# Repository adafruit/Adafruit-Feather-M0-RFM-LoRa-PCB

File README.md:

## Adafruit Feather M0 RFM LoRa PCB
&nbsp; <br />
Click to purchase from the Adafruit Shop:
- [Adafruit Feather M0 with RFM95 LoRa Radio - 900MHz - RadioFruit](https://www.adafruit.com/product/3178)
- [Adafruit Feather M0 RFM96 LoRa Radio - 433MHz - RadioFruit](https://www.adafruit.com/product/3179)

This is the Adafruit Feather M0 RFM95 LoRa Radio (900MHz). We call these RadioFruits, our take on an microcontroller with a "Long Range (LoRa)" packet radio transceiver with built in USB and battery charging. Its an Adafruit Feather M0 with a 900MHz radio module cooked in! Great for making wireless networks that are more flexible than Bluetooth LE and without the high power requirements of WiFi.

Feather is the new development board from Adafruit, and like its namesake it is thin, light, and lets you fly! We designed Feather to be a new standard for portable microcontroller cores.We have other boards in the Feather family, check'em out here.

This is the 900 MHz radio version, which can be used for either 868MHz or 915MHz transmission/reception - the exact radio frequency is determined when you load the software since it can be tuned around dynamically. We also sell a 433MHz version of the same radio chipset!

At the Feather M0's heart is an ATSAMD21G18 ARM Cortex M0 processor, clocked at 48 MHz and at 3.3V logic, the same one used in the new Arduino Zero. This chip has a whopping 256K of FLASH (8x more than the Atmega328 or 32u4) and 32K of RAM (16x as much)! This chip comes with built in USB so it has USB-to-Serial program & debug capability built in with no need for an FTDI-like chip.

For more details, check out the product pages at

  * https://www.adafruit.com/product/3178
  * https://www.adafruit.com/product/3179
  
PCB files for the Adafruit Feather M0 RFM69 / RFM9X LoRa Radios. The format is EagleCAD schematic and board layout

### License

Adafruit invests time and resources providing this open source design, please support Adafruit and open-source hardware by purchasing products from [Adafruit](https://www.adafruit.com)!

All text above must be included in any redistribution

Designed by Limor Fried/Ladyada for Adafruit Industries.
Creative Commons Attribution/Share-Alike, all text above must be included in any redistribution. 
See license.txt for additional information.

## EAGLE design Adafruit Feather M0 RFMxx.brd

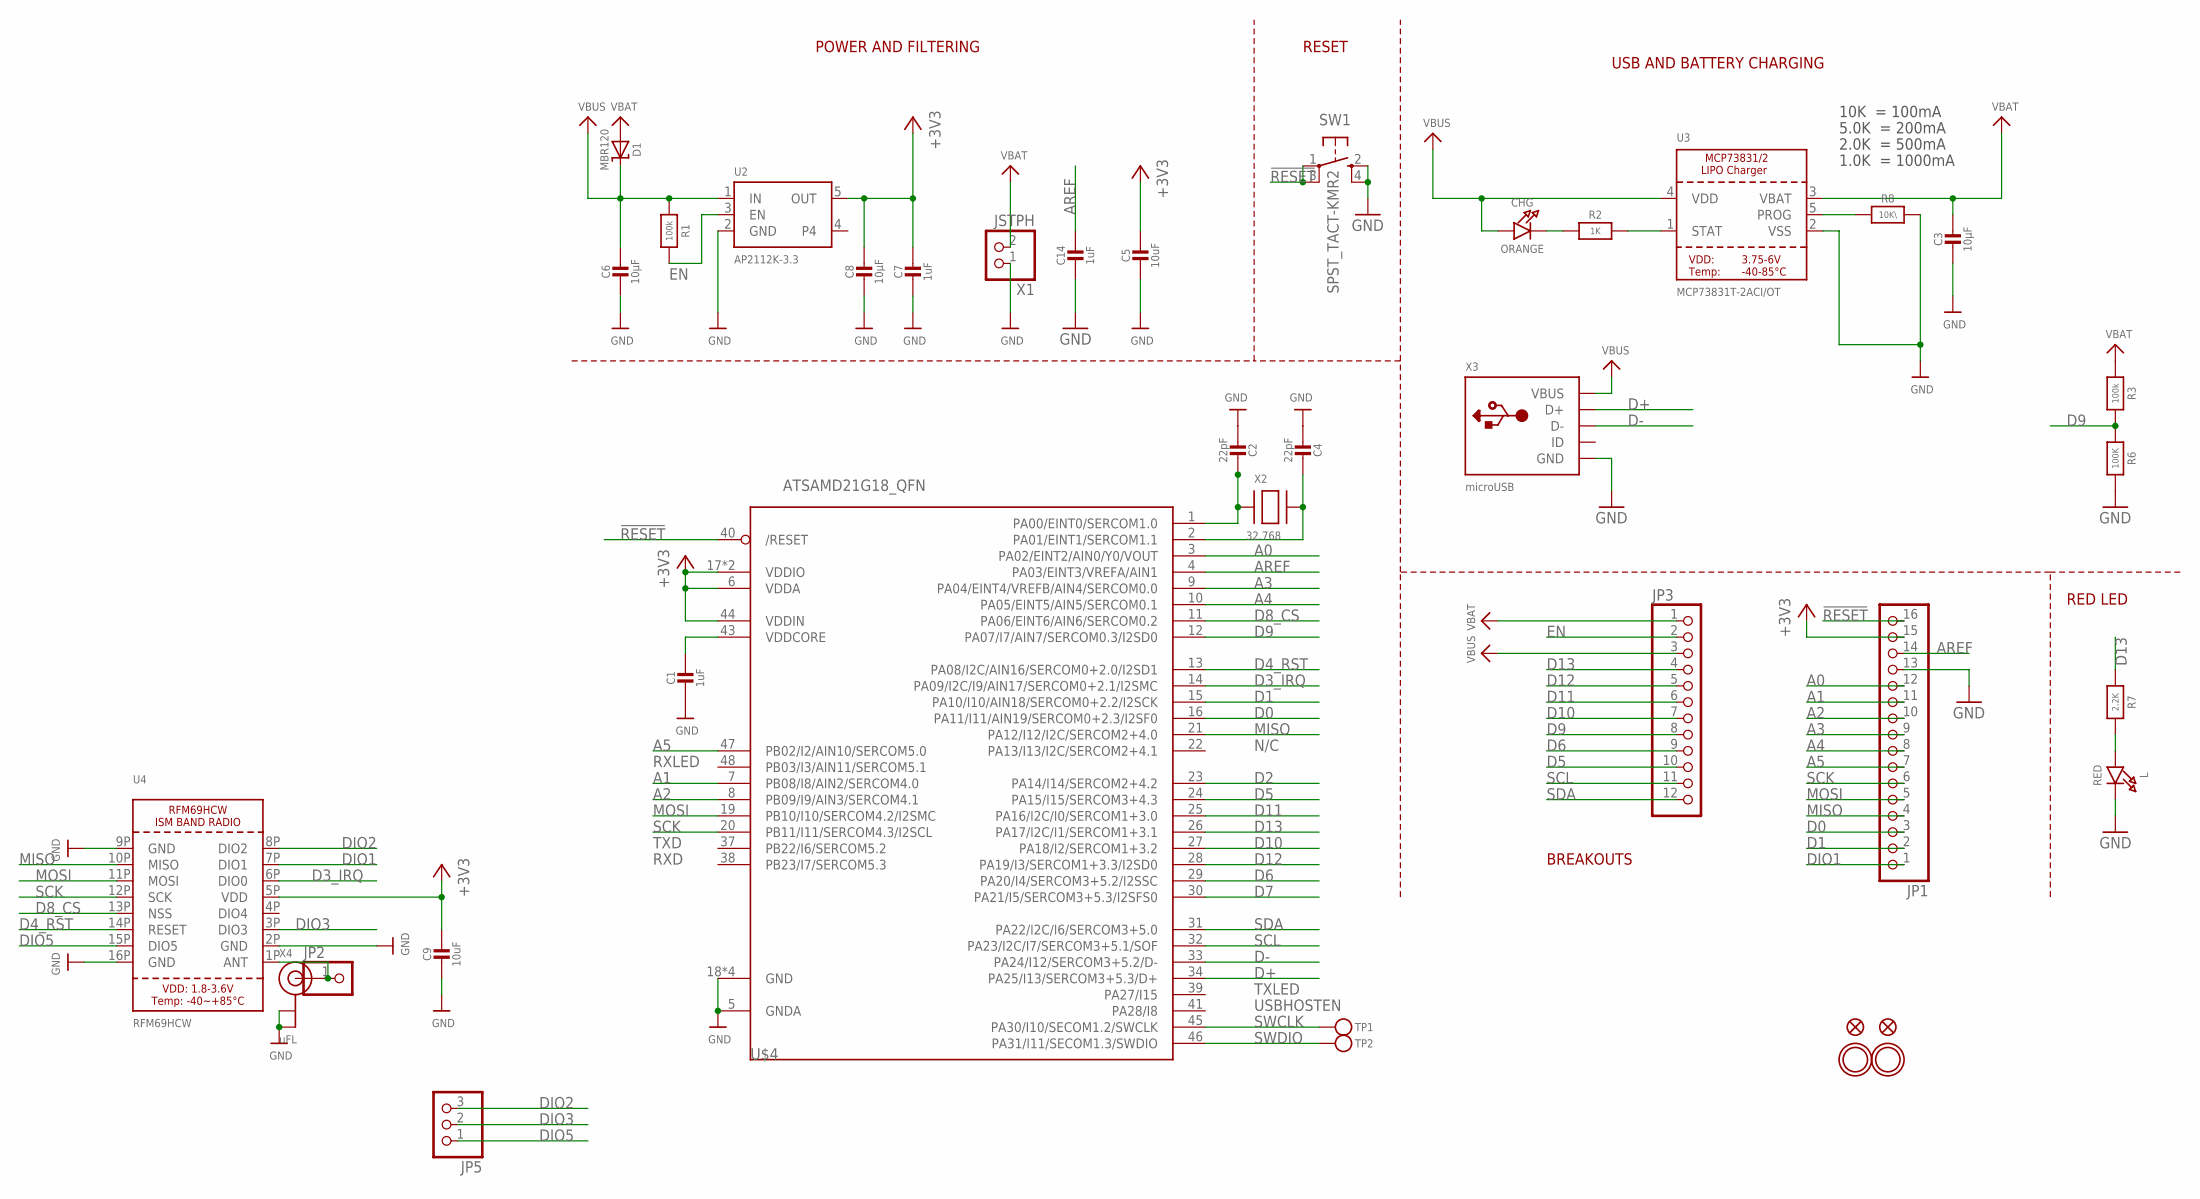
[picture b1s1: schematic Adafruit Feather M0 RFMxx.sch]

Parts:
C1, C7, C14: 1uF; 0603-NO
C2, C4: 22pF; 0603-NO
C3, C6, C8: 10µF; 0805-NO
C5, C9: 10uF; 0805-NO
CHG: ORANGE; CHIPLED_0805_NOOUTLINE
D1: MBR120; SOD-123
JP1: HEADER-1X16ROUND; 1X16_ROUND
JP2: HEADER-1X1ROUND; 1X01_ROUND
JP3: HEADER-1X12; 1X12_ROUND
JP5: HEADER-1X3ROUND; 1X03_ROUND
L: RED; CHIPLED_0805_NOOUTLINE
R1, R3: 100k; 0603-NO
R2: 1K; 0603-NO
R6: 100K; 0603-NO
R7: 2.2K; 0603-NO
R8: 10K\; 0603-NO
SW1: SPST_TACT-KMR2; KMR2
TP1, TP2: TESTPOINTROUND1.5MM; TESTPOINT_ROUND_1.5MM
U2: AP2112K-3.3; SOT23-5
U3: MCP73831T-2ACI/OT; SOT23-5
U4: RFM69HCW; RFMHCW_SMT
U$4: ATSAMD21G18_QFN; TQFN48_7MM
U$31, U$32: MOUNTINGHOLE2.5; MOUNTINGHOLE_2.5_PLATED
U$34, U$35: FIDUCIAL""; FIDUCIAL_1MM
X1: JSTPH; JSTPH2
X2: 32.768; XTAL3215
X3: microUSB; 4UCONN_20329_V2
X4: uFL; U.FL

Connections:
!RESET: JP1.16, SW1.1, SW1.3 (P1), U$4.40 (/RESET)
+3V3: C5.1, C7.1, C8.1, C9.1, JP1.15, U2.5 (OUT), U4.5P (VDD), U$4.6 (VDDA), U$4.17 (VDDIO), U$4.36 (VDDIO), U$4.44 (VDDIN)
A0: JP1.12, U$4.3 (PA02/EINT2/AIN0/Y0/VOUT)
A1: JP1.11, U$4.7 (PB08/I8/AIN2/SERCOM4.0)
A2: JP1.10, U$4.8 (PB09/I9/AIN3/SERCOM4.1)
A3: JP1.9, U$4.9 (PA04/EINT4/VREFB/AIN4/SERCOM0.0)
A4: JP1.8, U$4.10 (PA05/EINT5/AIN5/SERCOM0.1)
A5: JP1.7, U$4.47 (PB02/I2/AIN10/SERCOM5.0)
ANT: JP2.1, U4.1P (ANT), X4.3 (SIGNAL)
AREF: C14.1, JP1.14, U$4.4 (PA03/EINT3/VREFA/AIN1)
D0: JP1.3, U$4.16 (PA11/I11/AIN19/SERCOM0+2.3/I2SF0)
D1: JP1.2, U$4.15 (PA10/I10/AIN18/SERCOM0+2.2/I2SCK)
D2: U$4.23 (PA14/I14/SERCOM2+4.2)
D3_IRQ: U4.6P (DIO0), U$4.14 (PA09/I2C/I9/AIN17/SERCOM0+2.1/I2SMC)
D4_RST: U4.14P (RESET), U$4.13 (PA08/I2C/AIN16/SERCOM0+2.0/I2SD1)
D5: JP3.10, U$4.24 (PA15/I15/SERCOM3+4.3)
D6: JP3.9, U$4.29 (PA20/I4/SERCOM3+5.2/I2SSC)
D7: U$4.30 (PA21/I5/SERCOM3+5.3/I2SFS0)
D8_CS: U4.13P (NSS), U$4.11 (PA06/EINT6/AIN6/SERCOM0.2)
D9: JP3.8, R3.2, R6.1, U$4.12 (PA07/I7/AIN7/SERCOM0.3/I2SD0)
D10: JP3.7, U$4.27 (PA18/I2/SERCOM1+3.2)
D11: JP3.6, U$4.25 (PA16/I2C/I0/SERCOM1+3.0)
D12: JP3.5, U$4.28 (PA19/I3/SERCOM1+3.3/I2SD0)
D13: JP3.4, R7.1, U$4.26 (PA17/I2C/I1/SERCOM1+3.1)
D+: U$4.34 (PA25/I13/SERCOM3+5.3/D+), X3.D+
D-: U$4.33 (PA24/I12/SERCOM3+5.2/D-), X3.D-
DIO1: JP1.1, U4.7P (DIO1)
DIO2: JP5.3, U4.8P (DIO2)
DIO3: JP5.2, U4.3P (DIO3)
DIO5: JP5.1, U4.15P (DIO5)
EN: JP3.2, R1.2, U2.3 (EN)
GND: C1.2, C2.2, C3.2, C4.2, C5.2, C6.2, C7.2, C8.2, C9.2, C14.2, JP1.13, L.C, R6.2, R8.2, SW1.2 (S), SW1.4 (S1), U2.2 (GND), U3.2 (VSS), U4.2P (GND), U4.9P (GND), U4.16P (GND), U$4.5 (GNDA), U$4.18 (GND), U$4.35 (GND), U$4.42 (GND), U$4.THERMAL (GND), X1.1, X3.BASE@1 (GND), X3.BASE@2 (GND), X3.GND, X3.SPRT@1 (GND), X3.SPRT@2 (GND), X3.SPRT@3 (GND), X3.SPRT@4 (GND), X4.1 (GND), X4.2 (GND)
MISO: JP1.4, U4.10P (MISO), U$4.21 (PA12/I12/I2C/SERCOM2+4.0)
MOSI: JP1.5, U4.11P (MOSI), U$4.19 (PB10/I10/SERCOM4.2/I2SMC)
unnamed: CHG.C, R2.1
unnamed: L.A, R7.2
unnamed: R2.2, U3.1 (STAT)
unnamed: R8.1, U3.5 (PROG)
unnamed: C2.1, U$4.1 (PA00/EINT0/SERCOM1.0), X2.P$1
unnamed: C4.1, U$4.2 (PA01/EINT1/SERCOM1.1), X2.P$2
SCK: JP1.6, U4.12P (SCK), U$4.20 (PB11/I11/SERCOM4.3/I2SCL)
SCL: JP3.11, U$4.32 (PA23/I2C/I7/SERCOM3+5.1/SOF)
SDA: JP3.12, U$4.31 (PA22/I2C/I6/SERCOM3+5.0)
SWCLK: TP1.P$1, U$4.45 (PA30/I10/SECOM1.2/SWCLK)
SWDIO: TP2.P$1, U$4.46 (PA31/I11/SECOM1.3/SWDIO)
VBAT: C3.1, D1.A, JP3.1, R3.1, U3.3 (VBAT), X1.2
VBUS: C6.1, CHG.A, D1.C, JP3.3, R1.1, U2.1 (IN), U3.4 (VDD), X3.VBUS
VDDCORE: C1.1, U$4.43 (VDDCORE)

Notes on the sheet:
POWER AND FILTERING
RESET
10K = 100mA
5.0K = 200mA
2.0K = 500mA
1.0K = 1000mA
N/C
TXLED
USBHOSTEN
RXLED
TXD
RXD
USB AND BATTERY CHARGING
BREAKOUTS
RED LED

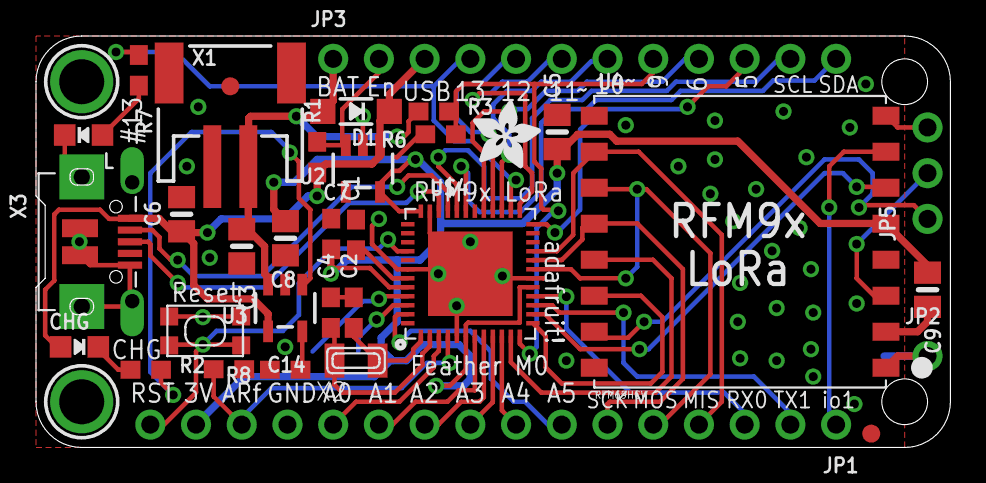
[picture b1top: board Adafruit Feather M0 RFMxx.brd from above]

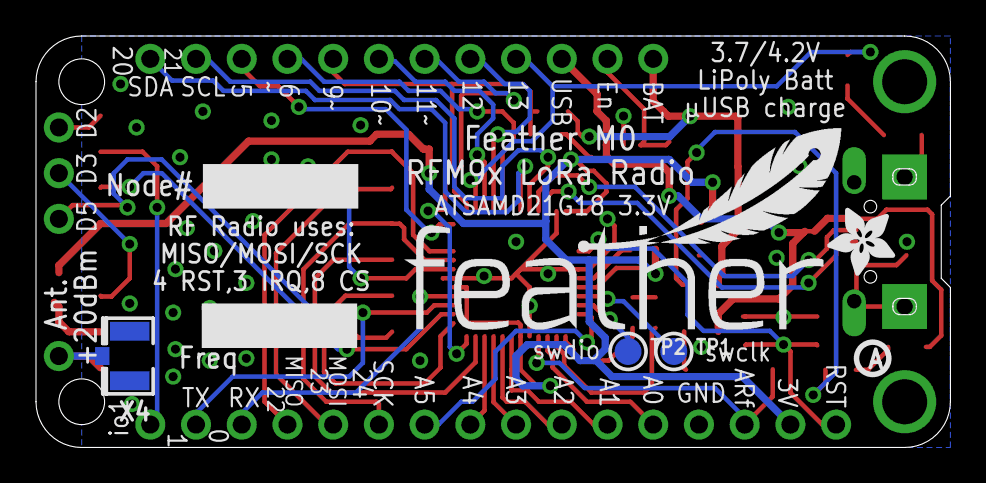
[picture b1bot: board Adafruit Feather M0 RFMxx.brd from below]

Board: 2 copper layers, 50.8 x 22.9 mm, 42 parts (6 on the bottom side), 46 nets.

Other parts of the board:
U$7, U$12: ADAFRUIT_3.5MM
U$9: FEATHERLOGO
U$13: PCBFEAT-REV-040

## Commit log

2016-06-08 init
2022-04-19 Added PrettyPins
2024-07-12 update prettypins

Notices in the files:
parts and their libraries:
microbuilder: This work is placed in the public domain, and may be freely used for commercial and non-commercial work with the following conditions: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
